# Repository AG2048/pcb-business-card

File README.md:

# pcb-business-card
Business card made using functional PCBs

Latest Revision: V1 (2025)

# Major Revisions:
## V1 (2025)
- Initial release of the PCB business card design.
- Design functions fully wirelessly, no need for any wired connections during operation. Maintains a slim profile (0.8mm thick PCB, with components on one side only).
- PCB dimensions: 85.6mm x 53.98mm (standard credit card size).
- Qi Wireless charging support -- Utilizes BQ51013B Qi Wireless Power Receiver IC to allow for wireless powering of the PCB business card in 5V 1A.
- NFC Tag support -- Utilizes ST25DV64K NFC Tag to allow for wirelessly programming of the RGB LED Matrix Display, while also allowing users to tap the card on their phone to load my website [andygong.com](https://andygong.com).
- RGB LED Matrix / Array Display -- Utilizes a 6x12 RGB LED Matrix of SK6805-EC15 LEDs to allow for colorful display of patterns that can be controlled by an on-board ATtiny84A microcontroller.
- The QR code on the back of the card can be scanned to load [andygong.com](https://andygong.com) as well.

PCB manufactured by [JLCPCB](https://jlcpcb.com/). Prototype boards assembled by [JLCPCB SMT Assembly Service](https://jlcpcb.com/smt-assembly). Further component sourcing and assembly done by myself.

### Images

#### Renders

#### Manufactured Board

#### Early Code Testing
`img/v1/v1_early_test.mov` -- Demonstrates simple patterns on the RGB LED Matrix, with an "Among Us" pixel art pattern shown at the end, which is data sent to the NFC tag by phone, and read by the ATTiny84 using I2C. The code snapshot is [HERE](https://github.com/AG2048/pcb-business-card/commit/e9710af22d912196d3559052da2425deacd2d185)

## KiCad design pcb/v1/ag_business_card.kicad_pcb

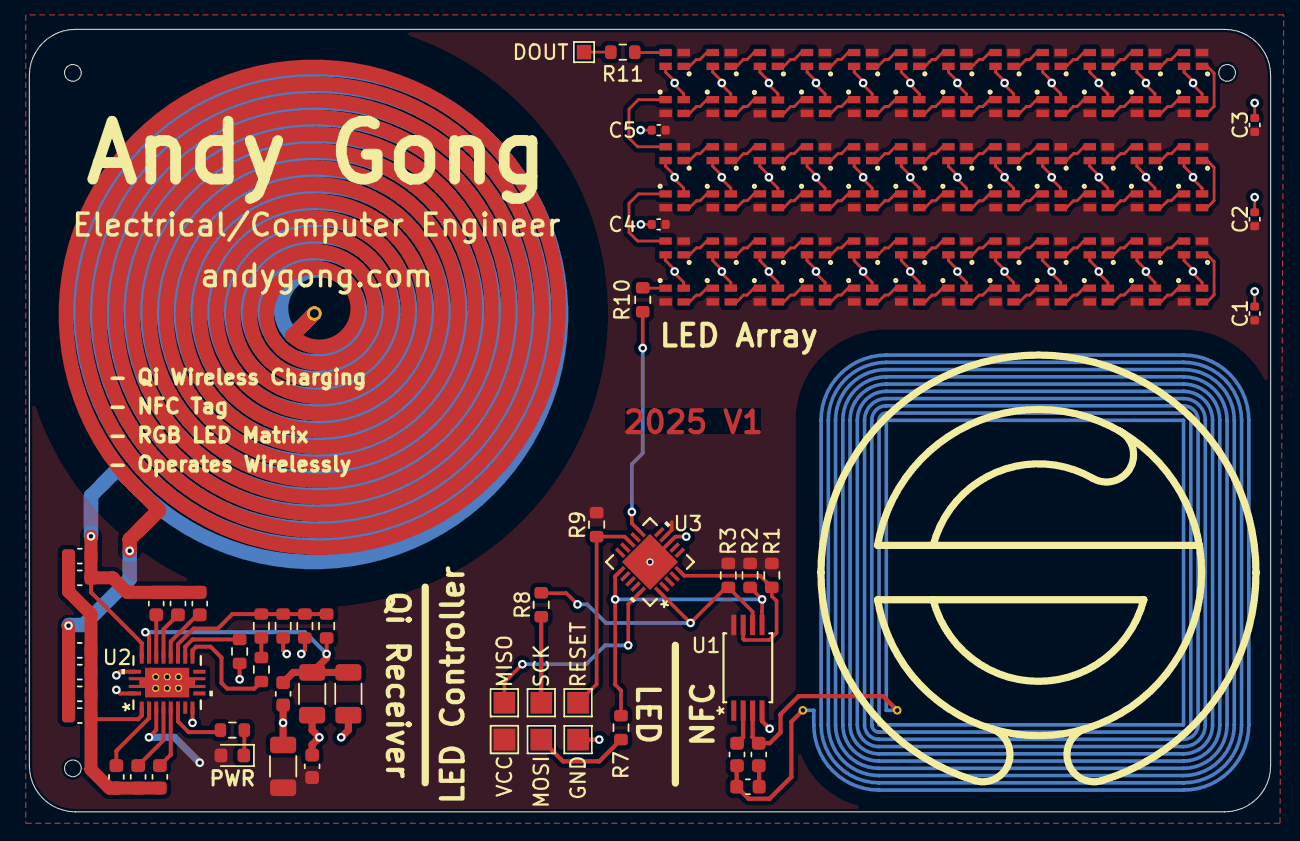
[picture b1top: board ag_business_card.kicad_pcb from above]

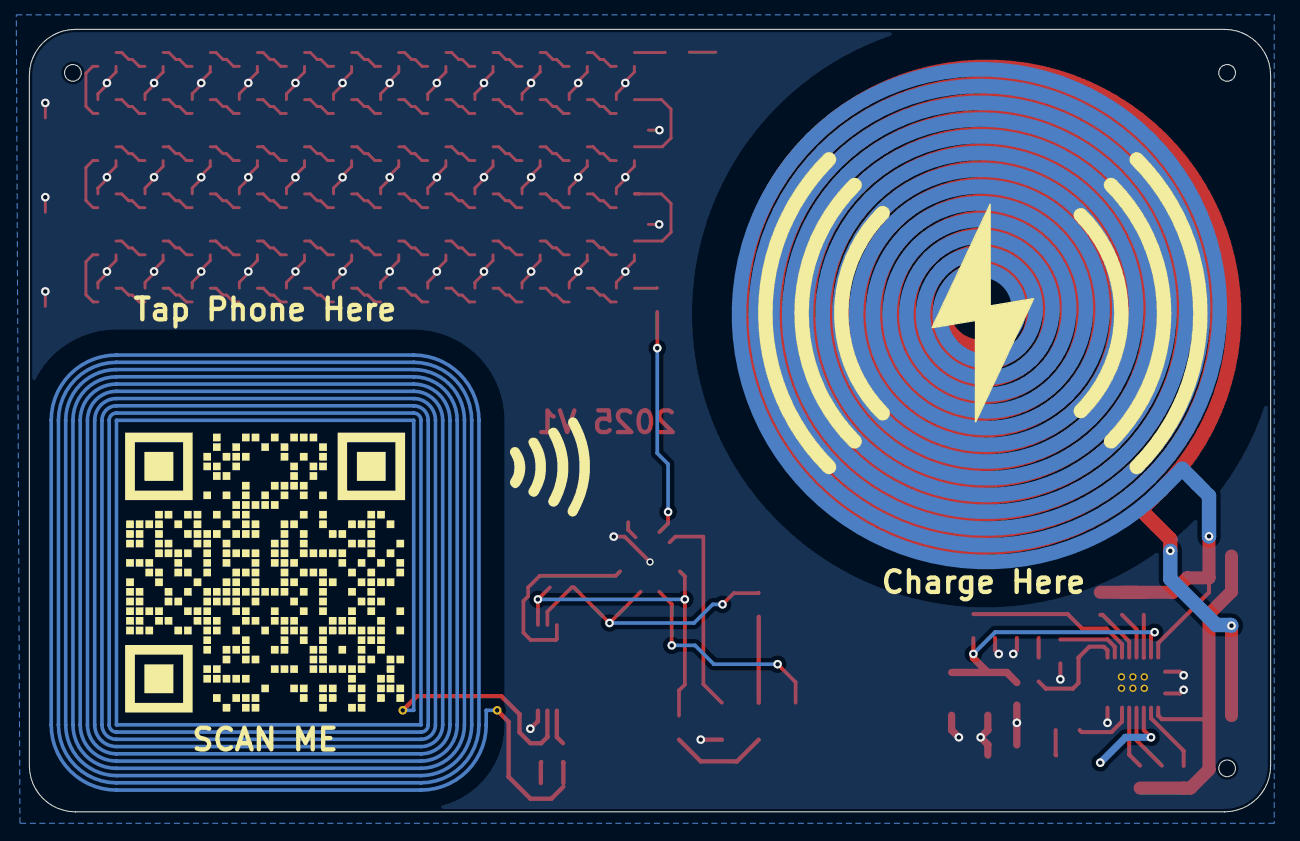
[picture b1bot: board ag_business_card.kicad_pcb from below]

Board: 2 copper layers, 85.6 x 54.0 mm, 126 parts (2 on the bottom side), 104 nets.

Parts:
C1, C2, C3, C4, C5: 100nF C307331; C_0402_1005Metric
C1_1, C1_2: 100nF; C_0603_1608Metric
C1_3: 10nF; C_0603_1608Metric
C1_4: 4.7nF; C_0603_1608Metric
C2_1: 2.2nF; C_0603_1608Metric
C2_2: 330pF; C_0603_1608Metric
C_BOOT1, C_BOOT2: 0.01uF 50V; C_0603_1608Metric
C_CLAMP1, C_CLAMP2: 0.47uF 25V; C_0603_1608Metric
C_COMM1, C_COMM2: 22nF 50V; C_0603_1608Metric
C_NFCPROT1: 1nF; C_0603_1608Metric
C_NFC_COIL1, C_NFC_COIL2: TBD; C_0603_1608Metric
C_OUT1: 10uF 50V; C_1206_3216Metric
C_OUT2: 0.1uF 50V; C_0603_1608Metric
C_RECT1, C_RECT2: 10uF 50V; C_1206_3216Metric
C_RECT3: 0.1uF 50V; C_0603_1608Metric
D1: 2.1V; LED_0603_1608Metric
DOUT: TestPoint_Pad_1.0x1.0mm
GND: TestPoint_Pad_1.5x1.5mm
MISO: TestPoint_Pad_1.5x1.5mm
MOSI: TestPoint_Pad_1.5x1.5mm
NFC_COIL1: 4.74uH; Final_NFC_COIL_4.7uH
Qi_COIL1: 9uH; Qi_COIL_9.9uH_L_11.836_L_prime_2_layer
R1, R2, R3, R9: 10k; R_0603_1608Metric
R4: 1k5; R_0603_1608Metric
R5, R6: 33; R_0603_1608Metric
R7, R8, R10, R11: 470; R_0603_1608Metric
RESET: TestPoint_Pad_1.5x1.5mm
R_FOD1: 220; R_0603_1608Metric
R_FOD2: 2k2; R_0603_1608Metric
R_OS1: 20k; R_0603_1608Metric
R_TS1: 10k; R_0603_1608Metric
SCAN ME: LOGO; qr_code_bmp
SCK: TestPoint_Pad_1.5x1.5mm
U1: ST25DV64K-IER6T3; TSSOP_V64K-IER6T3_STM
U2: BQ51013BRHLR; RHL20_2P05X3P05
U3: ATTINY84-20MUR; 20M1_ATM
U4, U5, U6, U7, U8, U9, U10, U11, U12, U13, U14, U15, U16, U17, U18, U19, U20, U21, U22, U23, U24, U25, U26, U27, U28, U29, U30, U31, U32, U33, U34, U35, U36, U37, U38, U39, U40, U41, U42, U43, U44, U45, U46, U47, U48, U49, U50, U51, U52, U53, U54, U55, U56, U57, U58, U59, U60, U61, U62, U63, U64, U65, U66, U67, U68, U69, U70, U71, U72, U73, U74, U75: 4492; 4492_ADA
VCC: TestPoint_Pad_1.5x1.5mm

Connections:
/Display/LED Array/DOUT: DOUT.1, R11.2
/Display/LED Array/R1OR2I: U15.3 (DOUT), U16.1 (DIN)
/Display/LED Array/R2OR3I: U27.3 (DOUT), U28.1 (DIN)
/Display/LED Array/R3OR4I: U39.3 (DOUT), U40.1 (DIN)
/Display/LED Array/R4OR5I: U51.3 (DOUT), U52.1 (DIN)
/Display/LED Array/R5OR6I: U63.3 (DOUT), U64.1 (DIN)
/Display/LED Array/R6O: R11.1, U75.3 (DOUT)
/Display/Processor/LED: R10.1, U3.11 (PB0_(PCINT8/XTAL1/CLKI))
/Display/Processor/MISO: MISO.1, U3.20 (PA5)
/Display/Processor/MOSI: MOSI.1, R7.1
/Display/Processor/RESET_n: R9.2, RESET.1, U3.13 (PB3_(PCINT11/RESET*/dW))
/Display/Processor/SCK: R8.2, SCK.1
/NFC/NFC_GPO: R1.2, U1.7, U3.5 ((ADC0/AREF/PCINT0)_PA0)
/NFC/NFC_SCL: R3.2, R8.1, U1.6 (SCL), U3.1 ((ADC4/USCK/SCL/T1/PCINT4)_PA4)
/NFC/NFC_SDA: R2.2, R7.2, U1.5 (SDA), U3.16 (PA6)
/Qi Charger/AC1: C1_1.1, C1_2.1, C1_3.1, C1_4.1, C2_1.2, C2_2.2, C_BOOT1.2, C_CLAMP1.2, C_COMM1.2, U2.2 (AC1)
/Qi Charger/AC2: C2_1.1, C2_2.1, C_BOOT2.1, C_CLAMP2.1, C_COMM2.1, Qi_COIL1.2, U2.19 (AC2)
/Qi Charger/BOOT1: C_BOOT1.1, U2.3 (BOOT1)
/Qi Charger/BOOT2: C_BOOT2.2, U2.17 (BOOT2)
/Qi Charger/CHG: R4.1, U2.7 (*CHG)
/Qi Charger/CLMP1: C_CLAMP1.1, U2.5 (CLMP1)
/Qi Charger/CLMP2: C_CLAMP2.2, U2.16 (CLMP2)
/Qi Charger/COIL1: C1_1.2, C1_2.2, C1_3.2, C1_4.2, Qi_COIL1.1
/Qi Charger/COM1: C_COMM1.1, U2.6 (COM1)
/Qi Charger/COM2: C_COMM2.2, U2.15 (COM2)
/Qi Charger/FOD: R6.1, R_FOD1.2, R_FOD2.2, R_OS1.2, U2.14 (FOD)
/Qi Charger/ILIM: R5.2, U2.12 (ILIM)
/Qi Charger/RECT: C_RECT1.2, C_RECT2.2, C_RECT3.2, R_OS1.1, U2.18 (RECT)
/Qi Charger/TS: R_TS1.1, U2.13 (TS-CTRL)
GND: C1.1, C2.1, C3.1, C4.1, C5.2, C_OUT1.1, C_OUT2.1, C_RECT1.1, C_RECT2.1, C_RECT3.1, GND.1, R_FOD1.1, R_FOD2.1, R_TS1.2, U1.4 (VSS), U2.1 (PGND), U2.9 (AD), U2.20 (PGND), U2.21 (EPAD), U3.8 (GND), U3.21 (PAD), U4.4 (GND), U5.4 (GND), U6.4 (GND), U7.4 (GND), U8.4 (GND), U9.4 (GND), U10.4 (GND), U11.4 (GND), U12.4 (GND), U13.4 (GND), U14.4 (GND), U15.4 (GND), U16.4 (GND), U17.4 (GND), U18.4 (GND), U19.4 (GND), U20.4 (GND), U21.4 (GND), U22.4 (GND), U23.4 (GND), U24.4 (GND), U25.4 (GND), U26.4 (GND), U27.4 (GND), U28.4 (GND), U29.4 (GND), U30.4 (GND), U31.4 (GND), U32.4 (GND), U33.4 (GND), U34.4 (GND), U35.4 (GND), U36.4 (GND), U37.4 (GND), U38.4 (GND), U39.4 (GND), U40.4 (GND), U41.4 (GND), U42.4 (GND), U43.4 (GND), U44.4 (GND), U45.4 (GND), U46.4 (GND), U47.4 (GND), U48.4 (GND), U49.4 (GND), U50.4 (GND), U51.4 (GND), U52.4 (GND), U53.4 (GND), U54.4 (GND), U55.4 (GND), U56.4 (GND), U57.4 (GND), U58.4 (GND), U59.4 (GND), U60.4 (GND), U61.4 (GND), U62.4 (GND), U63.4 (GND), U64.4 (GND), U65.4 (GND), U66.4 (GND), U67.4 (GND), U68.4 (GND), U69.4 (GND), U70.4 (GND), U71.4 (GND), U72.4 (GND), U73.4 (GND), U74.4 (GND), U75.4 (GND)
unnamed: C_NFCPROT1.2, C_NFC_COIL1.2, NFC_COIL1.1
unnamed: C_NFC_COIL1.1, C_NFC_COIL2.2
unnamed: D1.1 (K), R4.2
unnamed: R5.1, R6.2
unnamed: C_NFCPROT1.1, U1.2 (AC0)
unnamed: C_NFC_COIL2.1, NFC_COIL1.2, U1.3 (AC1)
unnamed: R10.2, U4.1 (DIN)
unnamed: U4.3 (DOUT), U5.1 (DIN)
unnamed: U5.3 (DOUT), U6.1 (DIN)
unnamed: U6.3 (DOUT), U7.1 (DIN)
unnamed: U7.3 (DOUT), U8.1 (DIN)
unnamed: U8.3 (DOUT), U9.1 (DIN)
unnamed: U9.3 (DOUT), U10.1 (DIN)
unnamed: U10.3 (DOUT), U11.1 (DIN)
unnamed: U11.3 (DOUT), U12.1 (DIN)
unnamed: U12.3 (DOUT), U13.1 (DIN)
unnamed: U13.3 (DOUT), U14.1 (DIN)
unnamed: U14.3 (DOUT), U15.1 (DIN)
unnamed: U16.3 (DOUT), U17.1 (DIN)
unnamed: U17.3 (DOUT), U18.1 (DIN)
unnamed: U18.3 (DOUT), U19.1 (DIN)
unnamed: U19.3 (DOUT), U20.1 (DIN)
unnamed: U20.3 (DOUT), U21.1 (DIN)
unnamed: U21.3 (DOUT), U22.1 (DIN)
unnamed: U22.3 (DOUT), U23.1 (DIN)
unnamed: U23.3 (DOUT), U24.1 (DIN)
unnamed: U24.3 (DOUT), U25.1 (DIN)
unnamed: U25.3 (DOUT), U26.1 (DIN)
unnamed: U26.3 (DOUT), U27.1 (DIN)
unnamed: U28.3 (DOUT), U29.1 (DIN)
unnamed: U29.3 (DOUT), U30.1 (DIN)
unnamed: U30.3 (DOUT), U31.1 (DIN)
unnamed: U31.3 (DOUT), U32.1 (DIN)
unnamed: U32.3 (DOUT), U33.1 (DIN)
unnamed: U33.3 (DOUT), U34.1 (DIN)
unnamed: U34.3 (DOUT), U35.1 (DIN)
unnamed: U35.3 (DOUT), U36.1 (DIN)
unnamed: U36.3 (DOUT), U37.1 (DIN)
unnamed: U37.3 (DOUT), U38.1 (DIN)
unnamed: U38.3 (DOUT), U39.1 (DIN)
unnamed: U40.3 (DOUT), U41.1 (DIN)
unnamed: U41.3 (DOUT), U42.1 (DIN)
unnamed: U42.3 (DOUT), U43.1 (DIN)
unnamed: U43.3 (DOUT), U44.1 (DIN)
unnamed: U44.3 (DOUT), U45.1 (DIN)
unnamed: U45.3 (DOUT), U46.1 (DIN)
unnamed: U46.3 (DOUT), U47.1 (DIN)
unnamed: U47.3 (DOUT), U48.1 (DIN)
unnamed: U48.3 (DOUT), U49.1 (DIN)
unnamed: U49.3 (DOUT), U50.1 (DIN)
unnamed: U50.3 (DOUT), U51.1 (DIN)
unnamed: U52.3 (DOUT), U53.1 (DIN)
unnamed: U53.3 (DOUT), U54.1 (DIN)
unnamed: U54.3 (DOUT), U55.1 (DIN)
unnamed: U55.3 (DOUT), U56.1 (DIN)
unnamed: U56.3 (DOUT), U57.1 (DIN)
unnamed: U57.3 (DOUT), U58.1 (DIN)
unnamed: U58.3 (DOUT), U59.1 (DIN)
unnamed: U59.3 (DOUT), U60.1 (DIN)
unnamed: U60.3 (DOUT), U61.1 (DIN)
unnamed: U61.3 (DOUT), U62.1 (DIN)
unnamed: U62.3 (DOUT), U63.1 (DIN)
unnamed: U64.3 (DOUT), U65.1 (DIN)
unnamed: U65.3 (DOUT), U66.1 (DIN)
unnamed: U66.3 (DOUT), U67.1 (DIN)
unnamed: U67.3 (DOUT), U68.1 (DIN)
unnamed: U68.3 (DOUT), U69.1 (DIN)
unnamed: U69.3 (DOUT), U70.1 (DIN)
unnamed: U70.3 (DOUT), U71.1 (DIN)
unnamed: U71.3 (DOUT), U72.1 (DIN)
unnamed: U72.3 (DOUT), U73.1 (DIN)
unnamed: U73.3 (DOUT), U74.1 (DIN)
unnamed: U74.3 (DOUT), U75.1 (DIN)
VCC: C1.2, C2.2, C3.2, C4.2, C5.1, C_OUT1.2, C_OUT2.2, D1.2 (A), R1.1, R2.1, R3.1, R9.1, U1.8 (VCC), U2.4 (OUT), U3.9 (VCC), U4.2 (VDD), U5.2 (VDD), U6.2 (VDD), U7.2 (VDD), U8.2 (VDD), U9.2 (VDD), U10.2 (VDD), U11.2 (VDD), U12.2 (VDD), U13.2 (VDD), U14.2 (VDD), U15.2 (VDD), U16.2 (VDD), U17.2 (VDD), U18.2 (VDD), U19.2 (VDD), U20.2 (VDD), U21.2 (VDD), U22.2 (VDD), U23.2 (VDD), U24.2 (VDD), U25.2 (VDD), U26.2 (VDD), U27.2 (VDD), U28.2 (VDD), U29.2 (VDD), U30.2 (VDD), U31.2 (VDD), U32.2 (VDD), U33.2 (VDD), U34.2 (VDD), U35.2 (VDD), U36.2 (VDD), U37.2 (VDD), U38.2 (VDD), U39.2 (VDD), U40.2 (VDD), U41.2 (VDD), U42.2 (VDD), U43.2 (VDD), U44.2 (VDD), U45.2 (VDD), U46.2 (VDD), U47.2 (VDD), U48.2 (VDD), U49.2 (VDD), U50.2 (VDD), U51.2 (VDD), U52.2 (VDD), U53.2 (VDD), U54.2 (VDD), U55.2 (VDD), U56.2 (VDD), U57.2 (VDD), U58.2 (VDD), U59.2 (VDD), U60.2 (VDD), U61.2 (VDD), U62.2 (VDD), U63.2 (VDD), U64.2 (VDD), U65.2 (VDD), U66.2 (VDD), U67.2 (VDD), U68.2 (VDD), U69.2 (VDD), U70.2 (VDD), U71.2 (VDD), U72.2 (VDD), U73.2 (VDD), U74.2 (VDD), U75.2 (VDD), VCC.1

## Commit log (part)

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2025-07-19 Add KiCad project files for V1 business card
    Added PCB layout, schematic, project, and symbol/footprint files for the AG Business Card V1, including display, NFC, Qi charger, and custom coil footprints. Also included a production ZIP archive fo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
2025-07-19 Add V1 front and back images
    Added images for V1, including front and back views, both in real life and composite formats. These images will be used for documentation or presentation purposes.
2025-07-19 Restructure PCB files and add code placeholder
    Moved all KiCad PCB design files and related assets from the V1 directory to pcb/v1 for improved organization. Added a placeholder ag_business_card.ino file for Arduino code in code/v1/ag_business_ca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
2025-07-19 Rename V1 image files to lowercase directory
    Moved image files from 'img/V1/' to 'img/v1/' to standardize directory naming to lowercase. No changes to file contents.
2025-07-19 Rename V1 image files to lowercase filenames
    Renamed image files in img/v1/ to use lowercase filenames for consistency and to avoid potential case-sensitivity issues.
2025-07-19 Update README with revision history and images
    Added a major revisions section for V1 (2025) and included render and manufactured board images to improve documentation and showcase the PCB business card design.
2025-07-19 Move PCB zip to production directory
    Renamed Full_Card_V1_2025-07-13_21-04-21.zip from pcb/v1/ to pcb/v1/production/ for better organization of production files.
2025-07-19 Add .gitignore file
    Added .gitignore to exclude .lck files and fp-info-cache directories from version control.
2025-07-19 Update README with new features and components
    Added details about Qi wireless charging, NFC tag support, RGB LED matrix, and fully wireless operation. Also included information on the BQ51013B power receiver, ST25DV64K NFC tag, and QR code funct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
2025-07-19 Add manufacturer info to README
    Included JLCPCB as the manufacturer in the project README for additional context.
2025-07-19 Update manufacturer info in README
    Clarified that JLCPCB both manufactured and assembled the product in the project documentation.
2025-07-19 Rename license files for clarity
    Renamed LICENSE.txt to LICENSE-CERN and code/LICENSE.txt to LICENSE-GPL to better reflect the specific licenses used in each file.
2025-07-20 Add initial AG Business Card V1 code and README
    Added a README with setup and requirements for the AG Business Card V1 project. Implemented initial Arduino code for the ATTiny84 to control a 6x12 RGB LED matrix and placeholder display patterns, wi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
2025-07-22 Limit LED brightness and add color cycling pattern
    Introduced MAX_BRIGHTNESS to prevent overpowering the LED matrix and replaced hardcoded brightness values with this constant. Added a new color cycling pattern to the LED display for enhanced visual 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
2025-07-22 Add LED matrix utility functions and 'AG' pattern
    Introduces utility functions for clearing the LED matrix and setting individual pixel colors, supporting a 6x12 matrix with zigzag wiring. Updates the loop to display a custom 'AG' pattern after the 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
2025-07-22 Add NFC read and display functionality to LED matrix
    Introduced NFC I2C read support and logic to display NFC data on the LED matrix. Refactored loop iteration to use a global variable and added a function to read 9 bytes from the NFC tag, mapping the 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
2025-07-22 Reduce LED brightness and simplify color cycling
    Lowered MAX_BRIGHTNESS from 63 to 15 to prevent overpowering the LEDs and adjusted the color cycling logic to match the new brightness range. This helps ensure safe operation and consistent color dis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
2025-07-22 Expand README with detailed hardware and encoding info
    Added comprehensive documentation on pin usage, LED matrix control, NFC I2C communication, and pattern encoding for the AG Business Card V1. The update includes explanations of memory optimizations, 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
2025-07-22 Refactor NFC I2C address variable and adjust delays
    Renamed NFC_ADDRESS to NFC_I2C_ADDRESS for clarity and updated all references. Reduced LED animation delay from 100ms to 10ms for faster visual feedback. Added clarification comment on bit order in N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
2025-07-22 Update README with NeoPixel library and bootloader info
    Added clarification about configuring the bootloader to use PORT B when using the tinyNeoPixel_Static library for the LED pin on ATTiny84.
2025-07-22 Add early code testing video and update README
    Added 'v1_early_test.mov' demonstrating simple patterns on the RGB LED Matrix, including an 'Among Us' pixel art pattern. Updated README to reference the video and provide context about the test and 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
2025-07-25 Update NFC I2C usage notes in README
    Added details about NFC tag password protection assumptions and initial 500 ms delay for tag power-up in the ATTiny84 startup sequence.
2025-07-25 Refactor LED matrix and NFC logic for frame-based display
    Reorganized code to support frame-based LED matrix animations loaded from NFC tag memory. Added functions for GRB444 and solid color frame display, transition handling, and improved pixel data manage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
2025-07-25 Add PCB business card project documentation
    Created docs/info.md to document the development procedures, research, and resources for the PCB business card project, including Qi charging, NFC tag, processor, and LED matrix design considerations.
2025-07-26 Expand design notes for NFC, processor, and LED matrix
    Added detailed explanations of design decisions and challenges for the NFC tag, processor selection, and LED matrix implementation. These notes provide more context on hardware choices, trade-offs, a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
2025-07-27 Set NFC address during initialization
    Assigns NFC_FIRST_ADDRESS to current_nfc_address at the start of the initialize() function to ensure proper NFC setup before proceeding.
2025-07-28 Implement smooth frame transition for LED matrix
    Replaced the previous buffer copy logic with a new transition algorithm that interpolates pixel values over time for smoother frame changes. Removed the unused leds_copy_from_buffer function and upda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
2025-07-28 Implement custom LED matrix display function
    Replaces tinyNeoPixel_Static library usage with a custom `leds_show()` function for sending pixel data to the RGB LED matrix. Adds low-level port manipulation and inline assembly for precise timing, 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
2025-07-29 Refactor LED assembly and add demo function
    Refactored the assembly code in leds_show() to use a bit counter and more compact structure for writing pixel data, improving maintainability and fitting within instruction limits. Added a demo() fun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
2025-07-29 Remove unused variable 'pin' from LED display code
    The 'pin' variable was declared but not used in the LED display section. This cleanup removes the redundant variable to improve code clarity.
2025-07-29 Expand and clarify NFC LED matrix documentation
    Extended the README with detailed explanations of the assembly code structure, frame metadata, code flow, and variable/function documentation for the NFC-driven LED matrix project. Clarified the hand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
2025-07-29 Add NFC memory address boundary check
    Introduced NFC_MAX_MEMORY_ADDRESS constant and updated nfc_read_data to validate that read operations do not exceed the maximum address for the ST25DV64K NFC tag.
2025-07-29 Update error handling and documentation for frame display
    Modified the error handling in the frame display loop to break and restart initialization on failure, instead of retrying indefinitely. Updated the README to clarify that the program restarts from in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
2025-07-29 Add script outline for NFC binary generation
    Created initial Python script with comments describing the intended functionality for generating a binary file for NFC tags from image and timing data.
2025-07-29 Add section on generate_nfc_binary.py usage
    Updated the README to include instructions and a description for the generate_nfc_binary.py script, explaining its purpose and usage for generating NFC tag binaries from images or GIFs.
2025-07-31 Improve NFC read function to handle large data
    Refactored the nfc_read_data function to read data from the NFC tag in chunks, supporting reads larger than the I2C buffer limit. Added constants for maximum read length and buffer size, and updated 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
2025-07-31 Adjust NFC buffer sizes and read length constants
    Reduced NFC_MAX_MEMORY_READ_LENGTH from 32 to 30 and set NFC_DATA_BUFFER_SIZE to PIXEL_ARRAY_SIZE to better align buffer size with pixel array requirements.
2025-07-31 Update V1 Board development notes in info.md
    Added detailed notes on code development for the V1 Board, including LED brightness adjustments, NFC tag reading improvements, structured data handling, LED display code modifications, and buffer siz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
2025-07-31 Add 500ms delay after LED error indication
    Inserted a 500ms delay after filling the LED matrix with solid red to indicate errors during NFC read and frame display operations. This provides clearer visual feedback for error states.
2025-07-31 Refactor transition handling in frame display functions
    Changed handle_transition from returning a bool to void and updated display_frame_grb444 and display_frame_solid_color to remove transition failure handling and always return true. This simplifies th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
2025-07-31 Rename pixel_data to dest_buffer in LED function
    Refactored leds_set_pixel_color_by_index to use 'dest_buffer' instead of 'pixel_data' for the destination array parameter and throughout the function for clarity and consistency.
2025-07-31 Add return value to initialize() function
    The initialize() function now explicitly returns true to indicate successful initialization. This clarifies the function's intent and return behavior.
2025-07-31 Update handle_transition comment for NFC usage
    Revised the comment in handle_transition() to clarify that the function always assumes success since it does not use NFC.
2025-08-01 Fix bitmask logic and pixel color packing in LED functions
    Corrects the calculation of pixel_data array indices and ensures proper bit masking when setting color channel values. Also fixes the color_mode bitmask logic in display_frame_solid_color() to assign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
2025-08-01 Add NFC binary generation and analysis utilities
    Implemented functions to process images and GIFs into 6x12 LED matrix frames, convert to 4-bit color, and generate NFC-compatible hex binary files. Added utilities for displaying, printing, and analy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
2025-08-01 Rename NFC hex file functions to bin file functions
    Refactored function names and related comments to use 'bin' instead of 'hex' for NFC binary file generation, printing, and analysis. Updated variable names and output file extensions accordingly for 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
2025-08-01 Add NFC tag size check and improve color mode output
    Added a file size check after generating the NFC binary to warn if the file exceeds the tag's capacity, and print remaining space if it fits. Enhanced the analyze_nfc_bin_file function to display col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
2025-09-25 Fixing #2 allowing single-color display mode
    Fixing #2. There are multiple causes. First is the repeated use of variable pixel_index, when iterating through the temp_pixel_data array, same value is also used inside the leds_set_pixel_color_by_i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
2025-09-25 Shorten demo() duration
    Decreased the delay in the demo function from 25ms to 5ms to speed up the LED animation and make transitions appear smoother.
2025-09-25 Comment out demo function in initialization
    The demo() function call used for testing the LED matrix has been commented out in the initialize() function. This prevents the demo from running during normal initialization.
2025-09-25 Move NFC power-up delay to setup function
    Relocated the 500ms delay for NFC tag power-up from the initialize() function to the setup() function. This is so we don't wait for I2C init upon the 2nd+ loop
